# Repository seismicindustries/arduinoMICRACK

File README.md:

# arduinoMICRACK

a eurorack mountable version of the arduino micro. 

by seismic industries - 2020

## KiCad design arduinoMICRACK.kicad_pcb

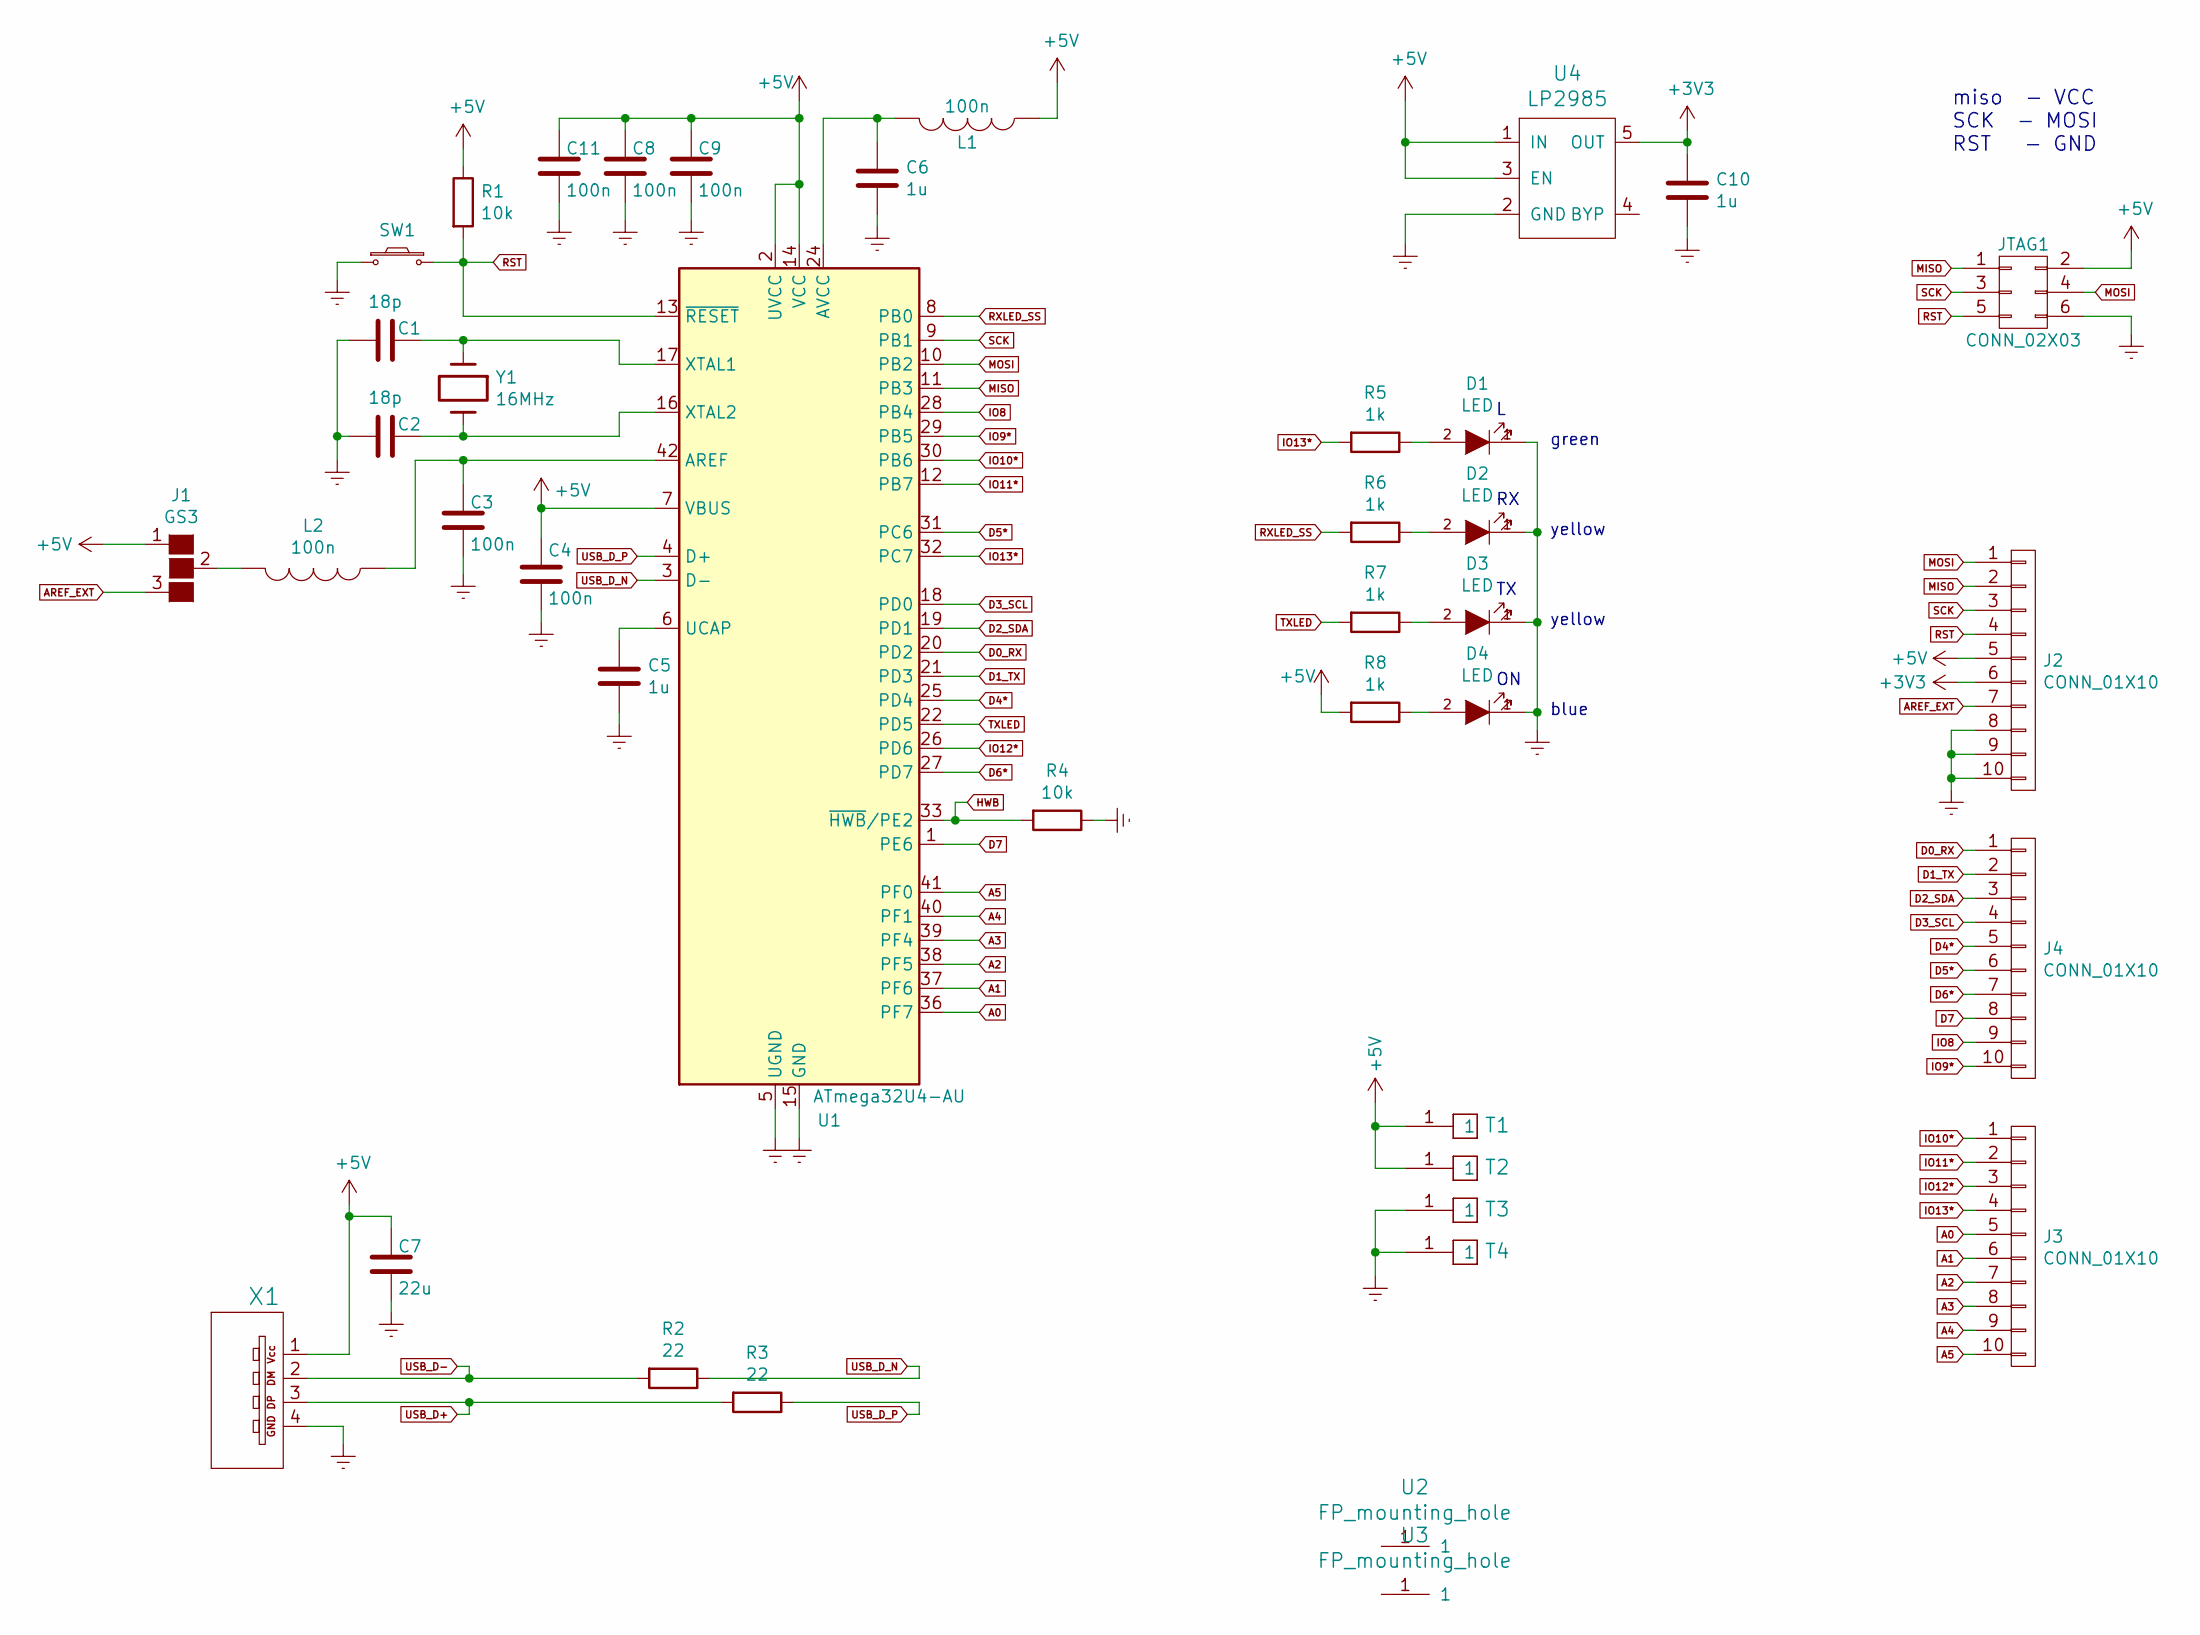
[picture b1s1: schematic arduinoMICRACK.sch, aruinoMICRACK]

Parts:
C1: 18p; KMS231_right_angle_switch_SMD_with_pegs; MPN VJ0805A180KXACBC
C2: 18p; C_0805; MPN VJ0805A180KXACBC
C3, C4, C8, C9, C11: 100n; C_0805; MPN 08055C104KAT2A
C5, C6, C10: 1u; C_0805; MPN UMK212B7105KG-T
C7: 22u; C_1210; MPN TMK325BJ226MM-P
D1, D2, D3, D4: LED; LED_D3.0mm; MPN LTL-4231N
J1: GS3; solderbridge
J2, J3, J4: CONN_01X10; Pin_Header_Straight_1x10_Pitch2.54mm_SMD
JTAG1: CONN_02X03; Pin_Header_Straight_2x03_Pitch2.54mm
L1, L2: 100n; Inductor_PSU_NLCV32T; MPN NLCV32T-R10M-PFR
R1, R4: 10k; R_0805; MPN CRCW080510K0FKEAC
R2, R3: 22; R_0805; MPN CRCW080522R0FKEA
R5, R6, R7, R8: 1k; R_0805; MPN CRCW08051K00FKEAC
SW1: SW_PUSH_SMALL_H; APEM_tactile_SMD_switch_6mm; MPN ADTSM66NV
T1, T2, T3, T4: TESTPIN; TESTPAD_SMD
U1: ATmega32U4-AU; TQFP-44_10x10mm_Pitch0.8mm; MPN ATMEGA32U4-AU
U2, U3: FP_mounting_hole; VIA_M3_mounting_hole
U4: LP2985; SOT-23-5; MPN LP2985-33DBVR
X1: Type B vertical; USB_TYPE_B_MUSB_Straight; MPN SS-52300-002
Y1: 16MHz; ABM7; MPN ABM7-16.000MHZ-D2Y-T

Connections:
+3V3: C10.2, J2.6, U4.5 (OUT)
+5V: C4.2, C7.2, C8.2, C9.2, C11.2, J1.1 (G1), J2.5, JTAG1.2, L1.1, R1.1, R8.2, T1.1, T2.1, U1.2 (UVCC), U1.7 (VBUS), U1.14 (VCC), U1.34 (VCC), U4.1 (IN), U4.3 (EN), X1.1
A0: J3.5, U1.36 (PF7)
A1: J3.6, U1.37 (PF6)
A2: J3.7, U1.38 (PF5)
A3: J3.8, U1.39 (PF4)
A4: J3.9, U1.40 (PF1)
A5: J3.10, U1.41 (PF0)
AREF_EXT: J1.3 (G3), J2.7
D0_RX: J4.1, U1.20 (PD2)
D1_TX: J4.2, U1.21 (PD3)
D2_SDA: J4.3, U1.19 (PD1)
D3_SCL: J4.4, U1.18 (PD0)
D4*: J4.5, U1.25 (PD4)
D5*: J4.6, U1.31 (PC6)
D6*: J4.7, U1.27 (PD7)
D7: J4.8, U1.1 (PE6)
Earth: C1.2, C2.2, C3.1, C4.1, C5.1, C6.1, C7.1, C8.1, C9.1, C10.1, C11.1, D1.1 (K), D2.1 (K), D3.1 (K), D4.1 (K), J2.8, J2.9, J2.10, JTAG1.6, R4.1, SW1.1, T3.1, T4.1, U1.5 (UGND), U1.15 (GND), U1.23 (GND), U1.35 (GND), U1.43 (GND), U4.2 (GND), X1.4
HWB: R4.2, U1.33 (~HWB~/PE2)
IO8: J4.9, U1.28 (PB4)
IO9*: J4.10, U1.29 (PB5)
IO10*: J3.1, U1.30 (PB6)
IO11*: J3.2, U1.12 (PB7)
IO12*: J3.3, U1.26 (PD6)
IO13*: J3.4, R5.2, U1.32 (PC7)
MISO: J2.2, JTAG1.1, U1.11 (PB3)
MOSI: J2.1, JTAG1.4, U1.10 (PB2)
unnamed: C1.1, U1.17 (XTAL1), Y1.1
unnamed: C2.1, U1.16 (XTAL2), Y1.2
unnamed: C3.2, L2.1, U1.42 (AREF)
unnamed: C5.2, U1.6 (UCAP)
unnamed: C6.2, L1.2, U1.24 (AVCC), U1.44 (AVCC)
unnamed: D1.2 (A), R5.1
unnamed: D2.2 (A), R6.1
unnamed: D3.2 (A), R7.1
unnamed: D4.2 (A), R8.1
unnamed: J1.2 (G2), L2.2
RST: J2.4, JTAG1.5, R1.2, SW1.2, U1.13 (~RESET)
RXLED_SS: R6.2, U1.8 (PB0)
SCK: J2.3, JTAG1.3, U1.9 (PB1)
TXLED: R7.2, U1.22 (PD5)
USB_D+: R3.2, X1.3
USB_D-: R2.2, X1.2
USB_D_N: R2.1, U1.3 (D-)
USB_D_P: R3.1, U1.4 (D+)

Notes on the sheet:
miso - VCC SCK - MOSI RST - GND
green
yellow
blue

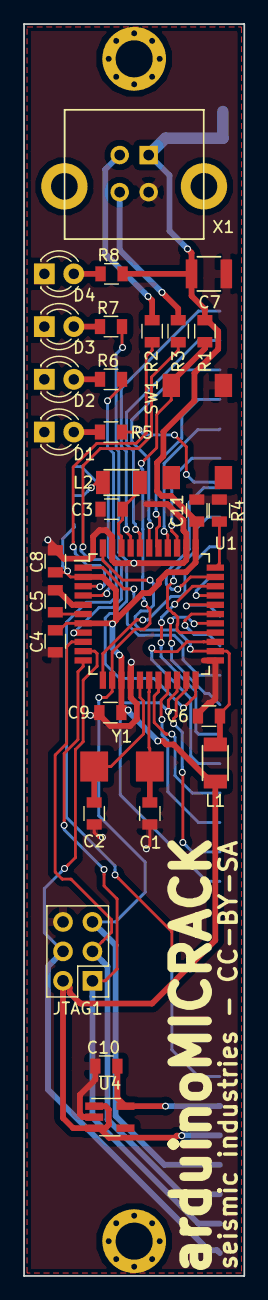
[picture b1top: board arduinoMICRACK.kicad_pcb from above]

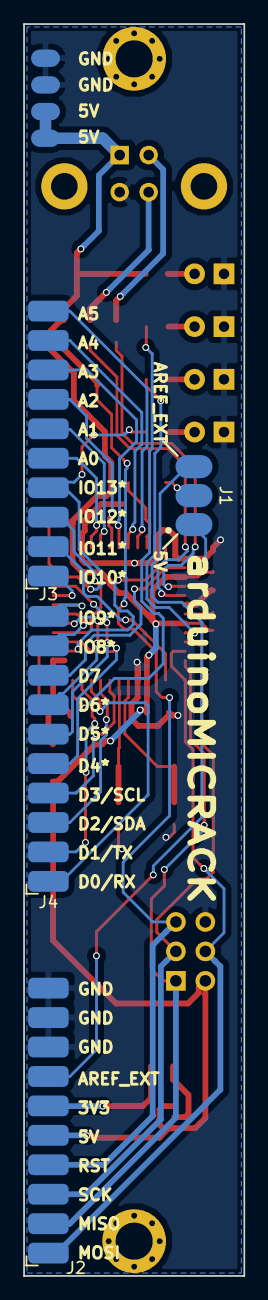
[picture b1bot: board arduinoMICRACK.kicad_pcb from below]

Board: 2 copper layers, 19.0 x 108.0 mm, 41 parts (8 on the bottom side), 45 nets.

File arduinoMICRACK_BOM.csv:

Refs,Value,Footprint,Quantity,MFR,MPN,SPR,SPNY1,16MHz,raffilibkicad:ABM7,1,Abracon,ABM7-16.000MHZ-D2Y-T,Mouser,815-ABM7-16-D2Y-TSW1,SW_PUSH_SMALL_H,raffilibkicad:APEM_tactile_SMD_switch_6mm,1,APEM,ADTSM66NV,Mouser,642-ADTSM66NVC3;C4;C9;C8;C11,100n,raffilibkicad:C_0805,5,AVX,08055C104KAT2A,Mouser,581-08055C104KC1;C2,18p,raffilibkicad:C_0805,2,Vishay,VJ0805A180KXACBC,Mouser,77-VJ0805A180KXACBCC5;C6;C10,1u,raffilibkicad:C_0805,3,Taiyo Yuden,UMK212B7105KG-T,Mouser,963-UMK212B7105KG-TC7,22u,raffilibkicad:C_1210,1,Taiyo Yuden,TMK325BJ226MM-P,Mouser,963-TMK325BJ226MM-PL1;L2,100n,raffilibkicad:Inductor_PSU_NLCV32T,2,TDK,NLCV32T-R10M-PFR,Mouser,810-NLCV32T-R10M-PFRD1;D2;D3;D4,LED,raffilibkicad:LED_D3.0mm,4,Lite-On,LTL-4231N,Mouser,859-LTL-4231NJTAG1,CONN_02X03,raffilibkicad:Pin_Header_Straight_2x03_Pitch2.54mm,1,-,-,Mouser,571-103777-3R1;R4,10k,raffilibkicad:R_0805,2,Vishay,CRCW080510K0FKEAC,Mouser,71-CRCW080510K0FKEACR5;R6;R7;R8,1k,raffilibkicad:R_0805,4,Vishay,CRCW08051K00FKEAC,Mouser,71-CRCW08051K00FKEACR2;R3,22,raffilibkicad:R_0805,2,Vishay,CRCW080522R0FKEA,Mouser,71-CRCW0805-22-E3U4,LP2985,raffilibkicad:SOT-23-5,1,Texas,LP2985-33DBVR,Mouser,595-LP2985-33DBVRU1,ATmega32U4-AU,raffilibkicad:TQFP-44_10x10mm_Pitch0.8mm,1,Atmega,ATMEGA32U4-AU,Mouser,556-ATMEGA32U4-AUX1,Type B vertical,raffilibkicad:USB_TYPE_B_MUSB_Straight,1,Stewart,SS-52300-002,Mouser,530-SS-52300-002

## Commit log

2020-08-17 first commit of the kicad files
2020-08-17 added pic
2020-08-17 updated link

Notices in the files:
arduinoMICRACK.kicad_pcb:
seismic industries - CC-BY-SA
